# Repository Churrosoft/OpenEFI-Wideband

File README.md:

# OpenEFI-Wideband
O2 Sensor visualizer

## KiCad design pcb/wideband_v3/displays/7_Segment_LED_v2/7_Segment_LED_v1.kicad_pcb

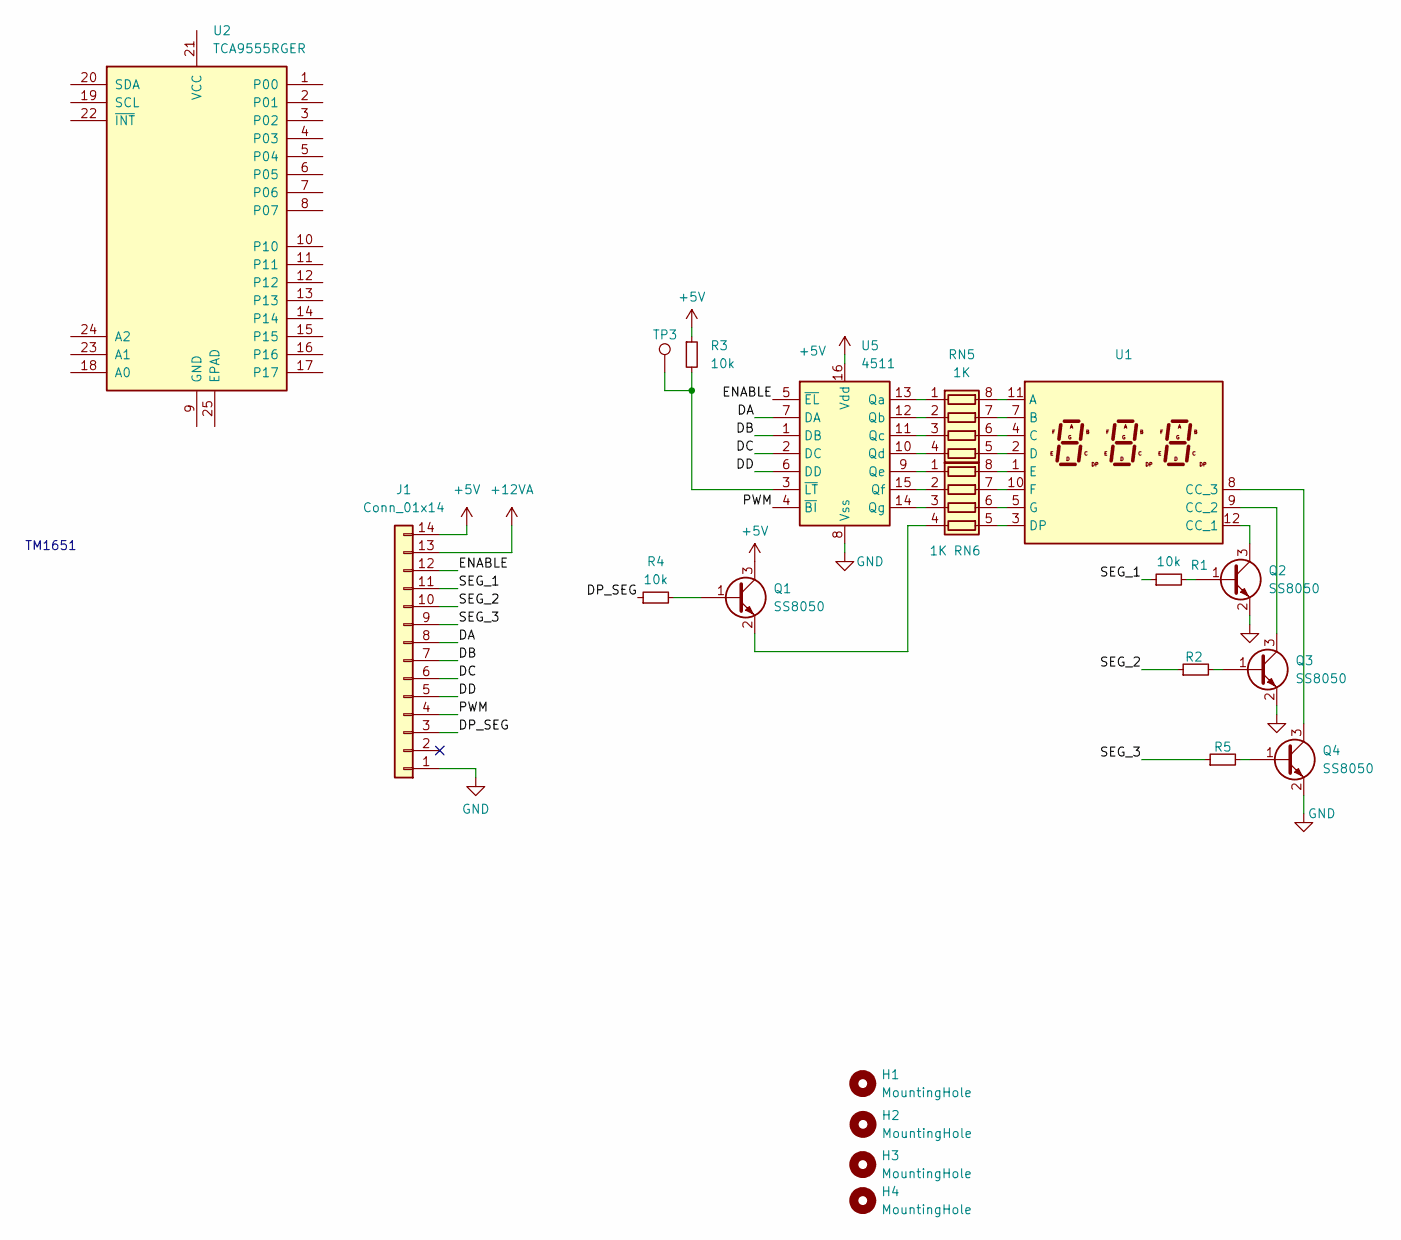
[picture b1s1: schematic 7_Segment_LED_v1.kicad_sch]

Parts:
H1, H2, H3, H4: MountingHole; MountingHole_3.2mm_M3_Pad_Via
J1: Conn_01x14; PinHeader_2x07_P2.54mm_Vertical
Q1, Q2, Q3, Q4: SS8050; SOT-23-3; LCSC C2150
R1, R2, R3, R4, R5: 10k; R_0603_1608Metric
RN5, RN6: 1K; R_Array_Convex_4x0603; LCSC C160614
TP3: TestPoint; TestPoint_Pad_1.0x1.0mm
U1: PinHeader_2x12_P2.00mm_Vertical
U2: TCA9555RGER; VQFN-24-1EP_4x4mm_P0.5mm_EP2.5x2.5mm
U5: 4511; SOP-16_4.55x10.3mm_P1.27mm; LCSC C5145431

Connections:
+5V: J1.14, Q1.3 (C), R3.1, U5.16 (Vdd)
+12VA: J1.13
/DA: J1.8, U5.7 (DA)
/DB: J1.7, U5.1 (DB)
/DC: J1.6, U5.2 (DC)
/DD: J1.5, U5.6 (DD)
/DP_SEG: J1.3, R4.1
/ENABLE: J1.12, U5.5 (~EL)
/PWM: J1.4, U5.4 (~BI)
/SEG_1: J1.11, R1.1
/SEG_2: J1.10, R2.1
/SEG_3: J1.9, R5.1
GND: J1.1, Q2.2 (E), Q3.2 (E), Q4.2 (E), U5.8 (Vss)
unnamed: Q1.1 (B), R4.2
unnamed: Q1.2 (E), RN6.4 (R4.1)
unnamed: Q2.1 (B), R1.2
unnamed: Q2.3 (C), U1.12 (CC_1)
unnamed: Q3.1 (B), R2.2
unnamed: Q3.3 (C), U1.9 (CC_2)
unnamed: Q4.1 (B), R5.2
unnamed: Q4.3 (C), U1.8 (CC_3)
unnamed: RN5.1 (R1.1), U5.13 (Qa)
unnamed: RN5.8 (R1.2), U1.11 (A)
unnamed: RN5.2 (R2.1), U5.12 (Qb)
unnamed: RN5.7 (R2.2), U1.7 (B)
unnamed: RN5.3 (R3.1), U5.11 (Qc)
unnamed: RN5.6 (R3.2), U1.4 (C)
unnamed: RN5.4 (R4.1), U5.10 (Qd)
unnamed: RN5.5 (R4.2), U1.2 (D)
unnamed: RN6.1 (R1.1), U5.9 (Qe)
unnamed: RN6.8 (R1.2), U1.1 (E)
unnamed: RN6.2 (R2.1), U5.15 (Qf)
unnamed: RN6.7 (R2.2), U1.10 (F)
unnamed: RN6.3 (R3.1), U5.14 (Qg)
unnamed: RN6.6 (R3.2), U1.5 (G)
unnamed: RN6.5 (R4.2), U1.3 (DP)
unnamed: R3.2, TP3.1, U5.3 (~LT)

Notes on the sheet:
TM1651

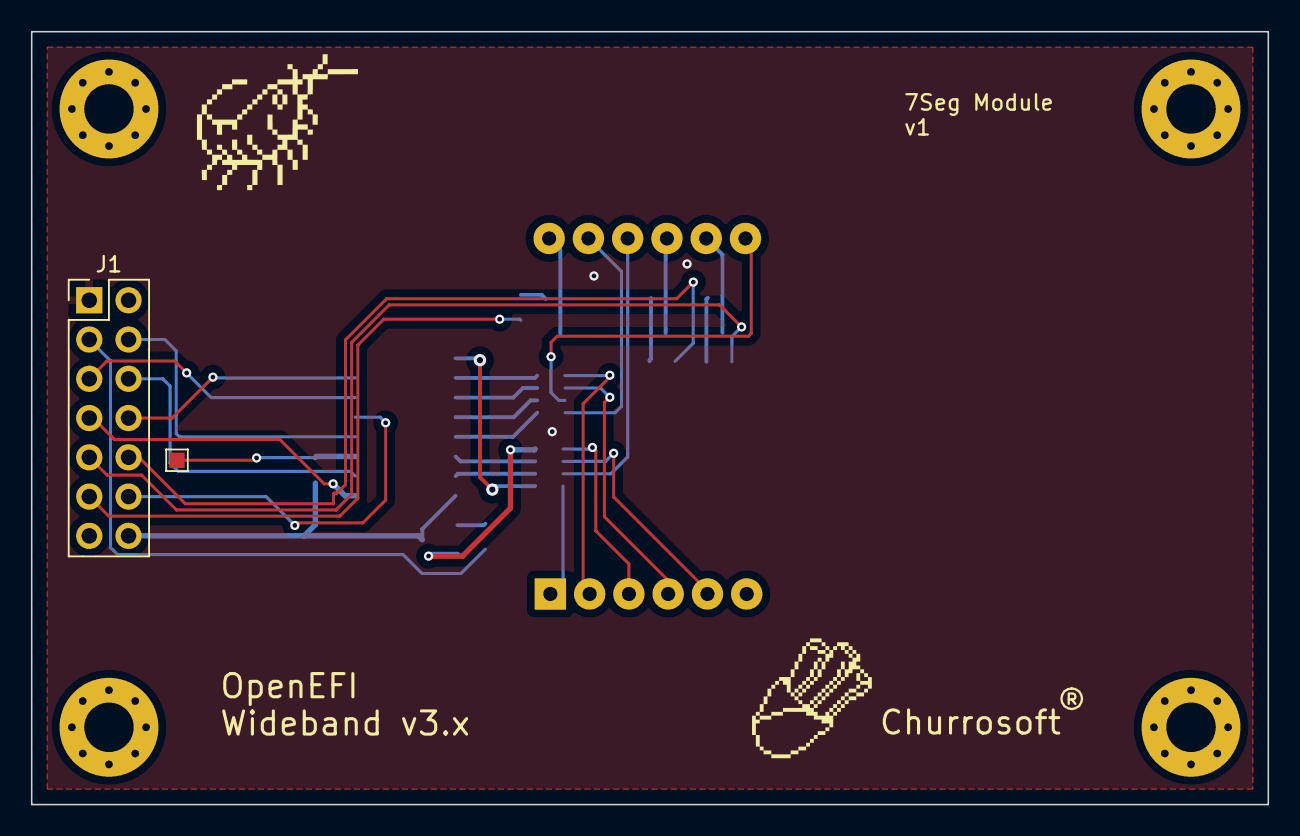
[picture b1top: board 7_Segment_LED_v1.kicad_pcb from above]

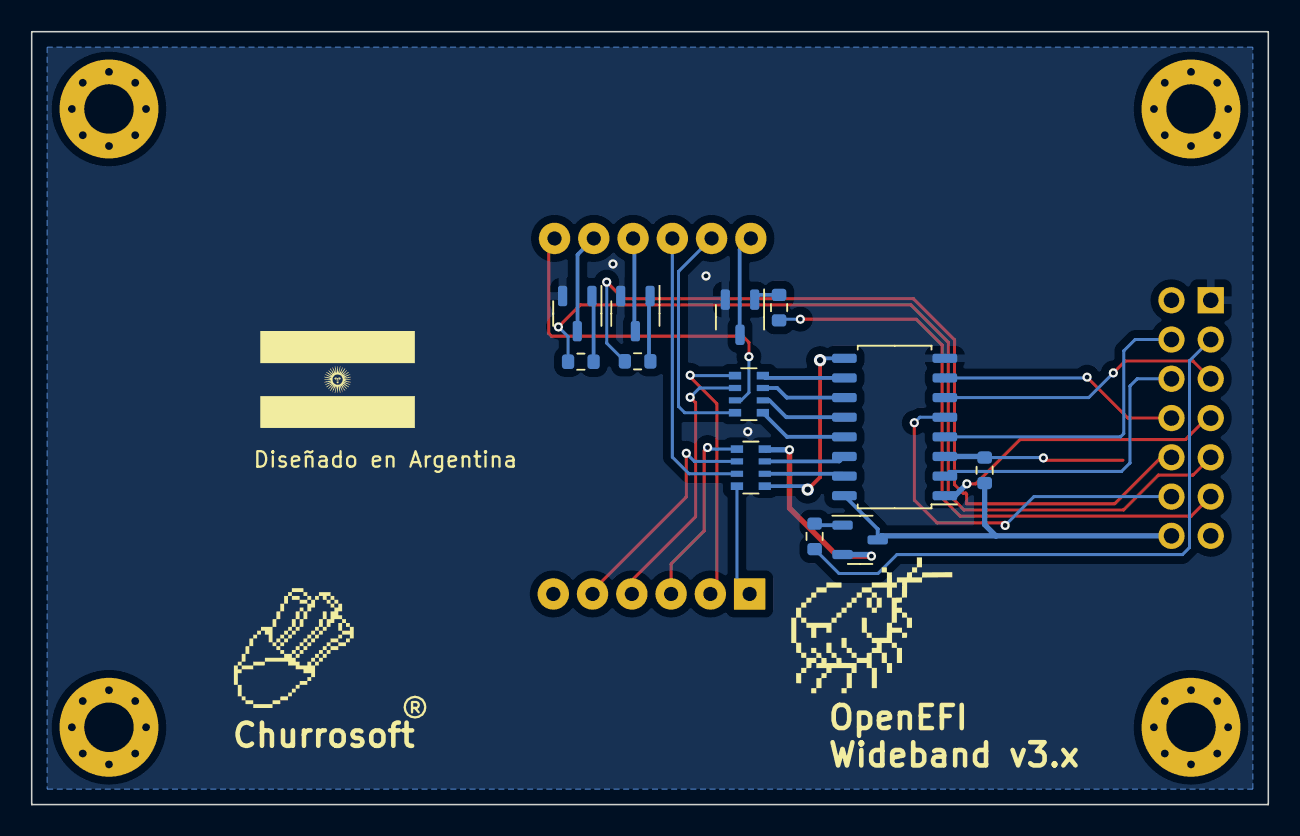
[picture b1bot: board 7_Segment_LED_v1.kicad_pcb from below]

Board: 2 copper layers, 80.0 x 50.0 mm, 19 parts (12 on the bottom side), 36 nets.

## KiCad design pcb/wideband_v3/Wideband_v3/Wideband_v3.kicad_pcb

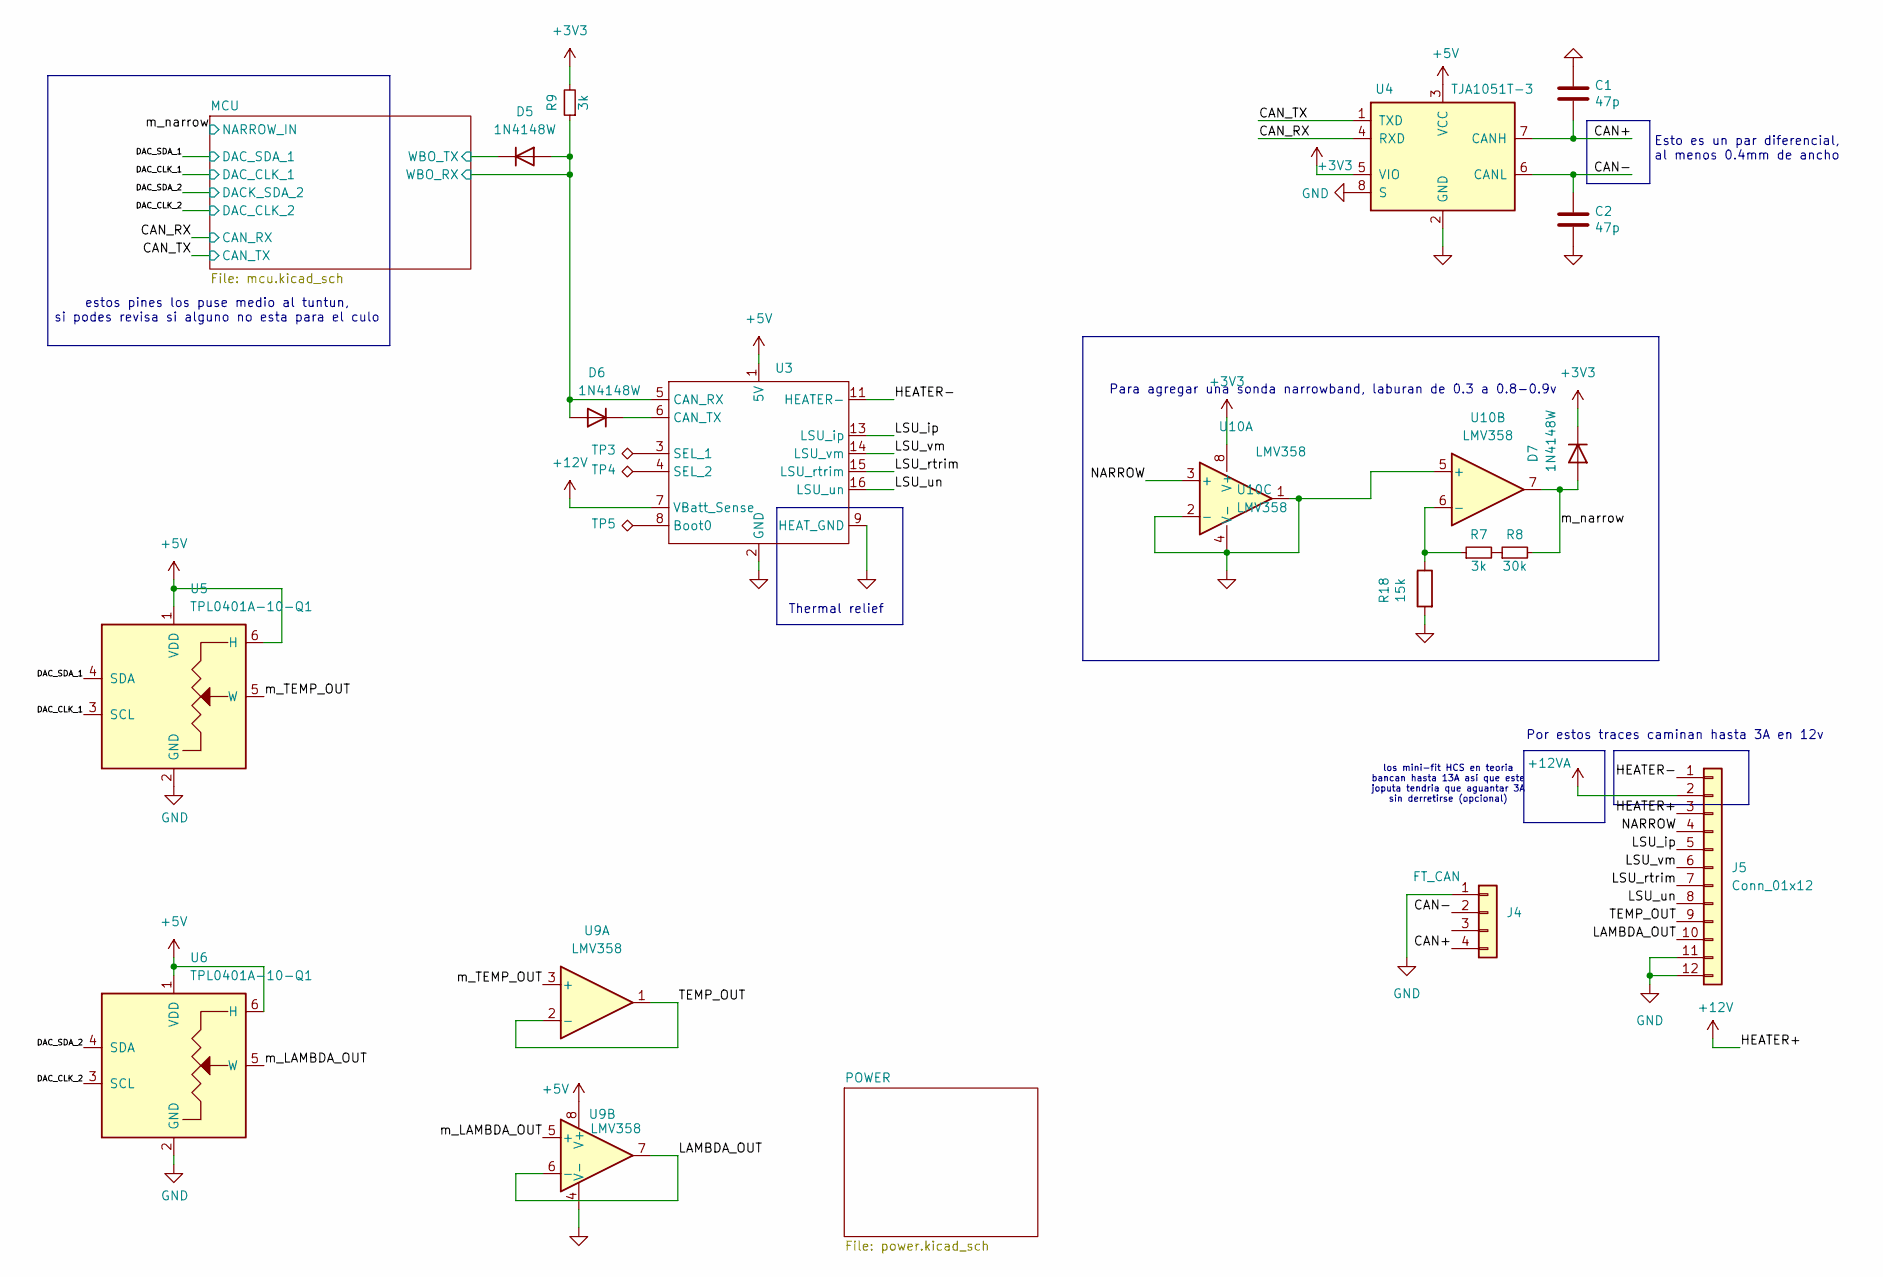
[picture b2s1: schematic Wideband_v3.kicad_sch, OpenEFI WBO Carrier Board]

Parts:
C1, C2: 47p; C_0402_1005Metric; LCSC C1567
D5, D6, D7: 1N4148W; D_SOD-323F
J4: FT_CAN; Molex_Mini-Fit_Jr_5566-04A_2x02_P4.20mm_Vertical; LCSC C586650
J5: Conn_01x12; Molex_Mini-Fit_Jr_5566-12A2_2x06_P4.20mm_Vertical
R7, R9: 3k; R_0603_1608Metric; LCSC C4211
R8: 30k; R_0603_1608Metric; LCSC C22984
R18: 15k; R_0603_1608Metric
TP3, TP4, TP5: TestPoint_Alt; TestPoint_Pad_1.0x1.0mm
U3: RusEFI_WBO
U4: TJA1051T-3; SOP-8_3.9x4.9mm_P1.27mm; LCSC C5342108
U5, U6: TPL0401A-10-Q1; Texas_R-PDSO-G6; LCSC C2666599
U9, U10: LMV358; SOIC-8_3.9x4.9mm_P1.27mm; LCSC C63813

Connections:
+3V3: D7.1 (K), R9.2, U4.5 (VIO), U10.8 (V+); also elsewhere on the board
+5V: U3.1 (5V), U4.3 (VCC), U5.1 (VDD), U5.6 (H), U6.1 (VDD), U6.6 (H), U9.8 (V+); also elsewhere on the board
+12V: J5.3, U3.7 (VBatt_Sense); also elsewhere on the board
+12VA: J5.2; also elsewhere on the board
/CAN+: C1.2, J4.4, U4.7 (CANH)
/CAN-: C2.1, J4.2, U4.6 (CANL)
/CAN_RX: U4.4 (RXD); also elsewhere on the board
/CAN_TX: U4.1 (TXD); also elsewhere on the board
/DAC_CLK_1: U5.3 (SCL); also elsewhere on the board
/DAC_CLK_2: U6.3 (SCL); also elsewhere on the board
/DAC_SDA_1: U5.4 (SDA); also elsewhere on the board
/DAC_SDA_2: U6.4 (SDA); also elsewhere on the board
/HEATER-: J5.1, U3.11 (HEATER-), U3.12 (HEATER-)
/LAMBDA_OUT: J5.10, U9.6 (-), U9.7
/LSU_ip: J5.5, U3.13 (LSU_ip)
/LSU_rtrim: J5.7, U3.15 (LSU_rtrim)
/LSU_un: J5.8, U3.16 (LSU_un)
/LSU_vm: J5.6, U3.14 (LSU_vm)
/MCU/WBO_RX: D5.2 (A), D6.2 (A), R9.1, U3.5 (CAN_RX); also elsewhere on the board
/MCU/WBO_TX: D5.1 (K); also elsewhere on the board
/NARROW: J5.4, U10.3 (+)
/TEMP_OUT: J5.9, U9.1, U9.2 (-)
/m_LAMBDA_OUT: U6.5 (W), U9.5 (+)
/m_TEMP_OUT: U5.5 (W), U9.3 (+)
/m_narrow: D7.2 (A), R8.2, U10.7; also elsewhere on the board
GND: C1.1, C2.2, J4.1, J5.11, J5.12, R18.2, U3.2 (GND), U3.9 (HEAT_GND), U3.10 (HEAT_GND2), U4.2 (GND), U4.8 (S), U5.2 (GND), U6.2 (GND), U9.4 (V-), U10.1, U10.2 (-), U10.4 (V-), U10.5 (+); also elsewhere on the board
unnamed: D6.1 (K), U3.6 (CAN_TX)
unnamed: R7.2, R8.1
unnamed: TP5.1, U3.8 (Boot0)
unnamed: TP3.1, U3.3 (SEL_1)
unnamed: TP4.1, U3.4 (SEL_2)
unnamed: R7.1, R18.1, U10.6 (-)

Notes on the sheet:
Thermal relief
Para agregar una sonda narrowband, laburan de 0.3 a 0.8-0.9v
Esto es un par diferencial, al menos 0.4mm de ancho
Por estos traces caminan hasta 3A en 12v
los mini-fit HCS en teoria bancan hasta 13A asi que este joputa tendria que aguantar 3A sin derretirse (opcional)
estos pines los puse medio al tuntun, si podes revisa si alguno no esta para el culo

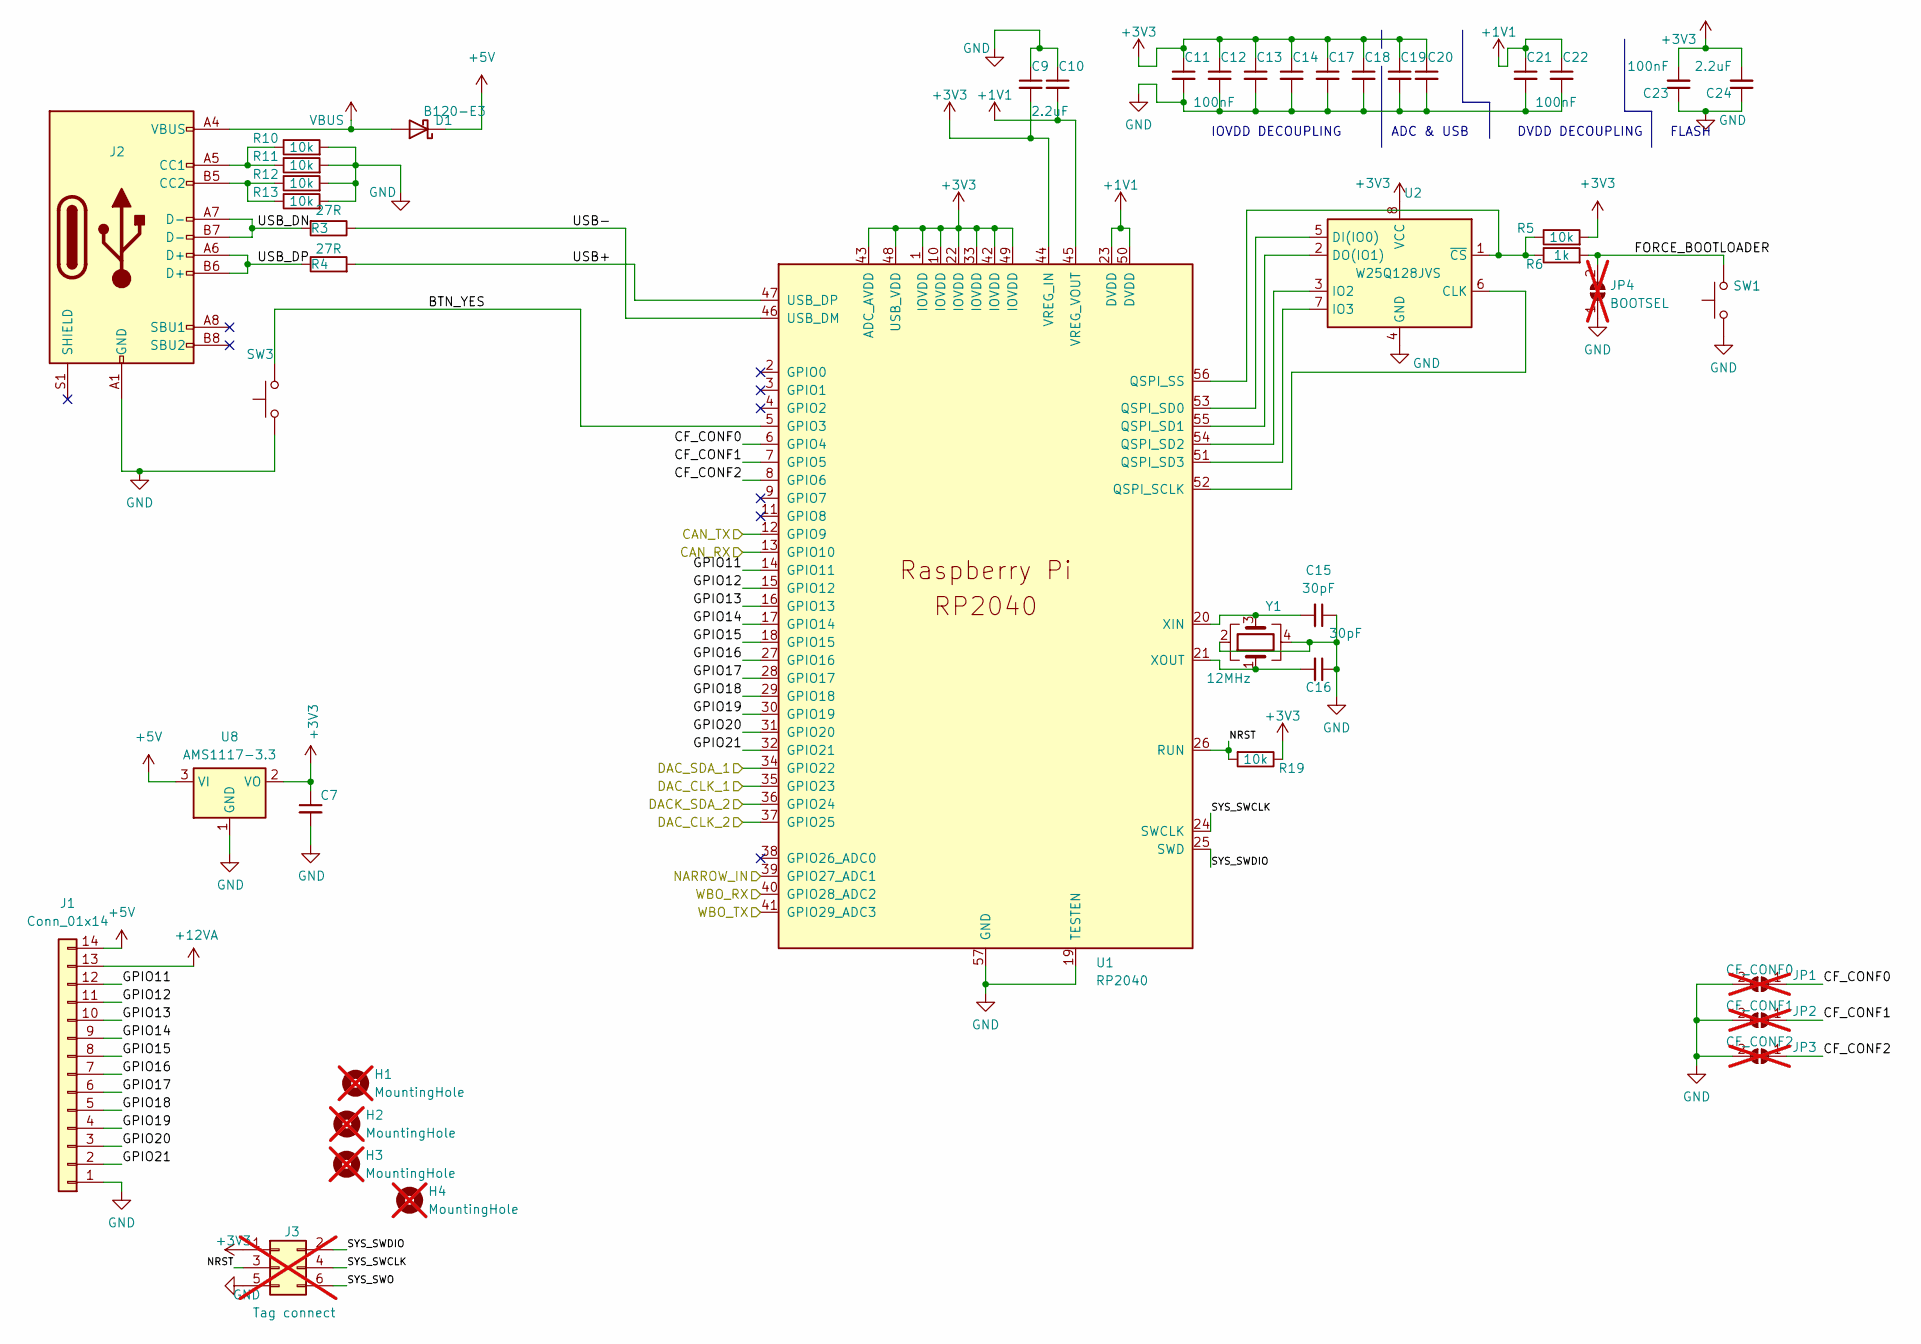
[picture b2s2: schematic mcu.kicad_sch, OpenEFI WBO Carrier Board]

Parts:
C7, C11, C12, C13, C14, C17, C18, C19, C20, C21, C22, C23: 100nF; C_0603_1608Metric; LCSC C14663
C9, C10, C24: 2.2uF; C_0805_2012Metric; LCSC C49217
C15, C16: 30pF; C_0402_1005Metric; LCSC C18164620
D1: B120-E3; D_SMA; LCSC C84343
H1, H2, H3, H4: MountingHole; MountingHole_3.2mm_M3_Pad_Via; not fitted
J1: Conn_01x14; PinHeader_2x07_P2.54mm_Vertical; LCSC C7494795
J2: USB_C_Receptacle_USB2.0; USB_C_Receptacle_HRO_TYPE-C-31-M-12; LCSC C165948
J3: Tag connect; Tag-Connect_TC2030-IDC-NL_2x03_P1.27mm_Vertical; not fitted
JP1: CF_CONF0; SolderJumper-2_P1.3mm_Open_TrianglePad1.0x1.5mm; not fitted
JP2: CF_CONF1; SolderJumper-2_P1.3mm_Open_TrianglePad1.0x1.5mm; not fitted
JP3: CF_CONF2; SolderJumper-2_P1.3mm_Open_TrianglePad1.0x1.5mm; not fitted
JP4: BOOTSEL; SolderJumper-2_P1.3mm_Open_TrianglePad1.0x1.5mm; not fitted
R3, R4: 27R; R_0603_1608Metric; LCSC C25190
R5, R10, R11, R12, R13, R19: 10k; R_0603_1608Metric; LCSC C115324
R6: 1k; R_0603_1608Metric; LCSC C21190
SW1: Key0; SW_Push_1P1T_XKB_TS-1187A; LCSC C412370
SW3: Key1; SW_SPST_Omron_B3F-315x_Angled; LCSC C2798927
U1: RP2040; QFN-56-1EP_7x7mm_P0.4mm_EP3.2x3.2mm; LCSC C2040
U2: W25Q128JVS; SOIC-8_5.23x5.23mm_P1.27mm; LCSC C97521
U8: AMS1117-3.3; SOT-223-3_TabPin2; LCSC C6186
Y1: 12MHz; Crystal_SMD_3225-4Pin_3.2x2.5mm; LCSC C9002

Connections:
+1V1: C10.2, C21.1, C22.1, U1.23 (DVDD), U1.45 (VREG_VOUT), U1.50 (DVDD)
+3V3: C7.1, C9.2, C11.1, C12.1, C13.1, C14.1, C17.1, C18.1, C19.1, C20.1, C23.2, C24.2, J3.1, R5.2, R19.1, U1.1 (IOVDD), U1.10 (IOVDD), U1.22 (IOVDD), U1.33 (IOVDD), U1.42 (IOVDD), U1.43 (ADC_AVDD), U1.44 (VREG_IN), U1.48 (USB_VDD), U1.49 (IOVDD), U2.8 (VCC), U8.2 (VO); also elsewhere on the board
+5V: D1.1 (K), J1.14, U8.3 (VI); also elsewhere on the board
+12VA: J1.13; also elsewhere on the board
/CAN_RX: U1.13 (GPIO10); also elsewhere on the board
/CAN_TX: U1.12 (GPIO9); also elsewhere on the board
/DAC_CLK_1: U1.35 (GPIO23); also elsewhere on the board
/DAC_CLK_2: U1.37 (GPIO25); also elsewhere on the board
/DAC_SDA_1: U1.34 (GPIO22); also elsewhere on the board
/DAC_SDA_2: U1.36 (GPIO24); also elsewhere on the board
/MCU/BTN_YES: SW3.2, U1.5 (GPIO3)
/MCU/CF_CONF0: JP1.1 (A), U1.6 (GPIO4)
/MCU/CF_CONF1: JP2.1 (A), U1.7 (GPIO5)
/MCU/CF_CONF2: JP3.1 (A), U1.8 (GPIO6)
/MCU/FORCE_BOOTLOADER: JP4.2 (B), R6.2, SW1.2
/MCU/GPIO11: J1.12, U1.14 (GPIO11)
/MCU/GPIO12: J1.11, U1.15 (GPIO12)
/MCU/GPIO13: J1.10, U1.16 (GPIO13)
/MCU/GPIO14: J1.9, U1.17 (GPIO14)
/MCU/GPIO15: J1.8, U1.18 (GPIO15)
/MCU/GPIO16: J1.7, U1.27 (GPIO16)
/MCU/GPIO17: J1.6, U1.28 (GPIO17)
/MCU/GPIO18: J1.5, U1.29 (GPIO18)
/MCU/GPIO19: J1.4, U1.30 (GPIO19)
/MCU/GPIO20: J1.3, U1.31 (GPIO20)
/MCU/GPIO21: J1.2, U1.32 (GPIO21)
/MCU/NRST: J3.3, R19.2, U1.26 (RUN)
/MCU/SYS_SWCLK: J3.4, U1.24 (SWCLK)
/MCU/SYS_SWDIO: J3.2, U1.25 (SWD)
/MCU/SYS_SWO: J3.6
/MCU/USB+: R4.2, U1.47 (USB_DP)
/MCU/USB-: R3.1, U1.46 (USB_DM)
/MCU/USB_DN: J2.A7 (D-), J2.B7 (D-), R3.2
/MCU/USB_DP: J2.A6 (D+), J2.B6 (D+), R4.1
/MCU/WBO_RX: U1.40 (GPIO28_ADC2); also elsewhere on the board
/MCU/WBO_TX: U1.41 (GPIO29_ADC3); also elsewhere on the board
/m_narrow: U1.39 (GPIO27_ADC1); also elsewhere on the board
GND: C7.2, C9.1, C10.1, C11.2, C12.2, C13.2, C14.2, C15.1, C16.1, C17.2, C18.2, C19.2, C20.2, C21.2, C22.2, C23.1, C24.1, J1.1, J2.A1 (GND), J2.A12 (GND), J2.B1 (GND), J2.B12 (GND), J3.5, JP1.2 (B), JP2.2 (B), JP3.2 (B), JP4.1 (A), R10.2, R11.2, R12.2, R13.2, SW1.1, SW3.1, U1.19 (TESTEN), U1.57 (GND), U2.4 (GND), U8.1 (GND), Y1.2, Y1.4; also elsewhere on the board
unnamed: J2.A5 (CC1), R10.1, R11.1
unnamed: J2.B5 (CC2), R12.1, R13.1
unnamed: U1.52 (QSPI_SCLK), U2.6 (CLK)
unnamed: U1.53 (QSPI_SD0), U2.5 (DI(IO0))
unnamed: U1.55 (QSPI_SD1), U2.2 (DO(IO1))
unnamed: U1.54 (QSPI_SD2), U2.3 (IO2)
unnamed: U1.51 (QSPI_SD3), U2.7 (IO3)
unnamed: R5.1, R6.1, U1.56 (QSPI_SS), U2.1 (~CS)
unnamed: C15.2, U1.20 (XIN), Y1.3
unnamed: C16.2, U1.21 (XOUT), Y1.1
VBUS: D1.2 (A), J2.A4 (VBUS), J2.A9 (VBUS), J2.B4 (VBUS), J2.B9 (VBUS)

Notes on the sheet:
FLASH
ADC & USB
DVDD DECOUPLING
IOVDD DECOUPLING

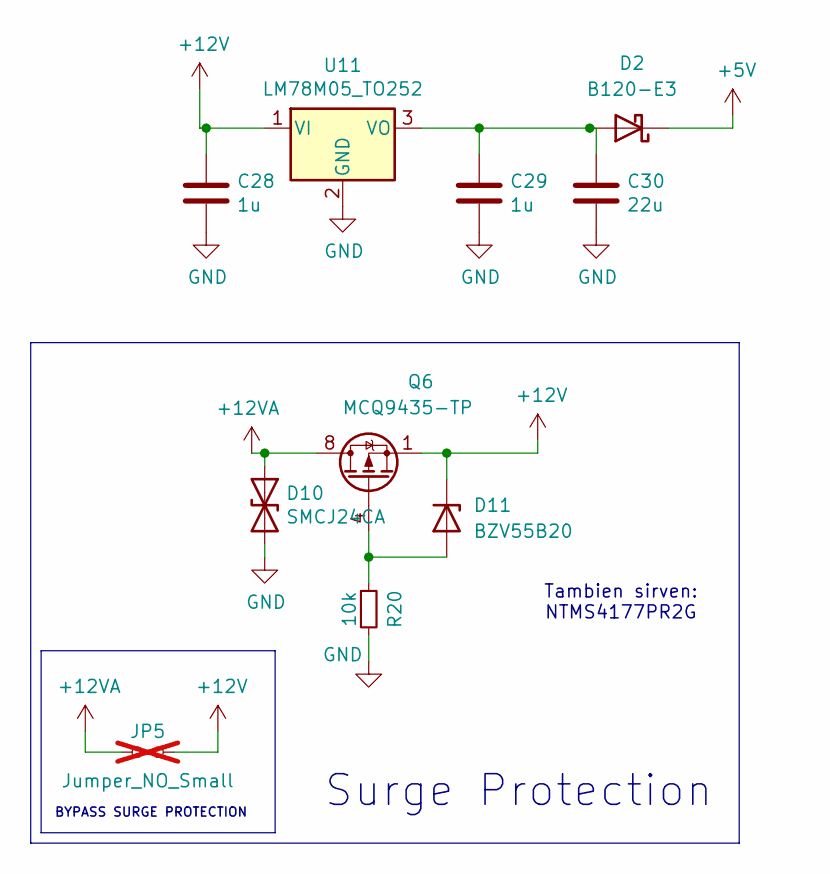
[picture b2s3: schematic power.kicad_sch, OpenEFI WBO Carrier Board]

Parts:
C28, C29: 1u; C_0603_1608Metric; LCSC C15849
C30: 22u; C_0805_2012Metric; LCSC C45783
D2: B120-E3; D_SMA; LCSC C84343
D10: SMCJ24CA; D_SMC; LCSC C151279
D11: BZV55B20; D_MiniMELF; LCSC C550392
JP5: Jumper_NO_Small; SolderJumper-2_P1.3mm_Open_RoundedPad1.0x1.5mm; not fitted
Q6: MCQ9435-TP; SOIC-8_3.9x4.9mm_P1.27mm; LCSC C586650
R20: 10k; R_0603_1608Metric; LCSC C115324
U11: LM78M05_TO252; TO-252-2; LCSC C58069

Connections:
+5V: D2.1 (K); also elsewhere on the board
+12V: C28.1, D11.1 (K), JP5.2, Q6.1 (S), Q6.2 (S), Q6.3 (S), U11.1 (VI); also elsewhere on the board
+12VA: D10.1 (A1), JP5.1, Q6.5 (D), Q6.6 (D), Q6.7 (D), Q6.8 (D); also elsewhere on the board
GND: C28.2, C29.2, C30.2, D10.2 (A2), R20.2, U11.2 (GND); also elsewhere on the board
unnamed: C29.1, C30.1, D2.2 (A), U11.3 (VO)
unnamed: D11.2 (A), Q6.4 (G), R20.1

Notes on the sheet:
BYPASS SURGE PROTECTION
Tambien sirven: NTMS4177PR2G
Surge Protection

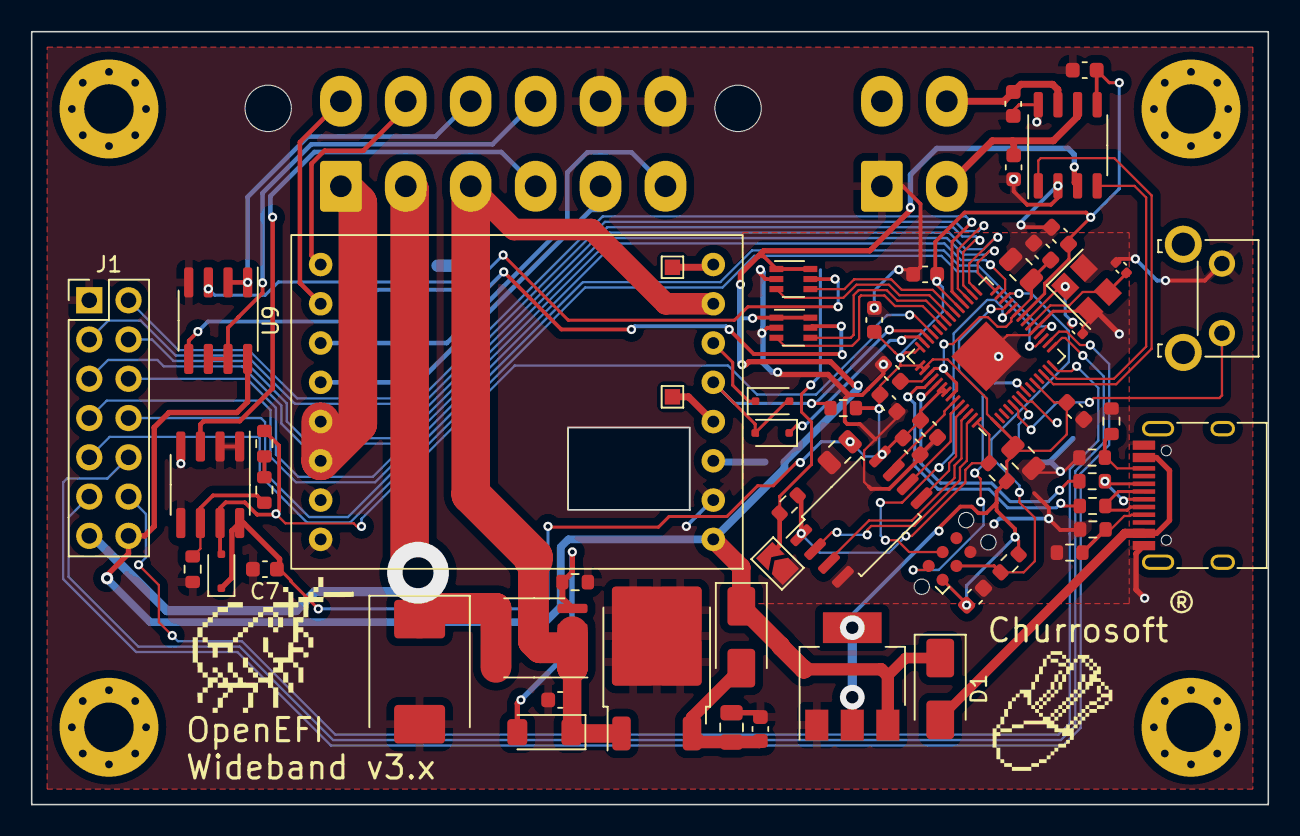
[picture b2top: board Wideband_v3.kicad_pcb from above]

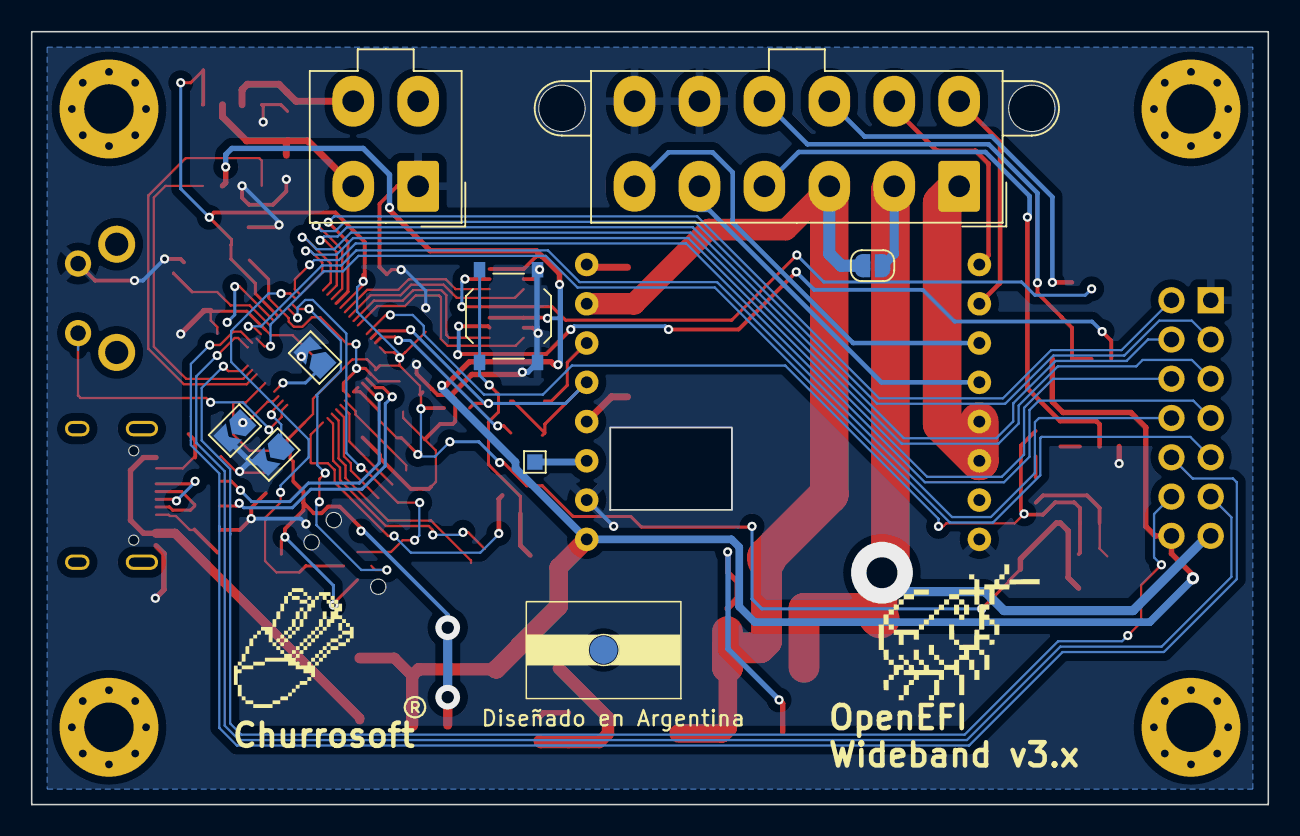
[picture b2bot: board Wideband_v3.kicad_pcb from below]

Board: 2 copper layers, 80.0 x 50.0 mm, 74 parts (8 on the bottom side), 69 nets.

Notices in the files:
pcb/wideband_v3/Wideband_v3.kicad_sch:
CERN-OHL-S Licence
